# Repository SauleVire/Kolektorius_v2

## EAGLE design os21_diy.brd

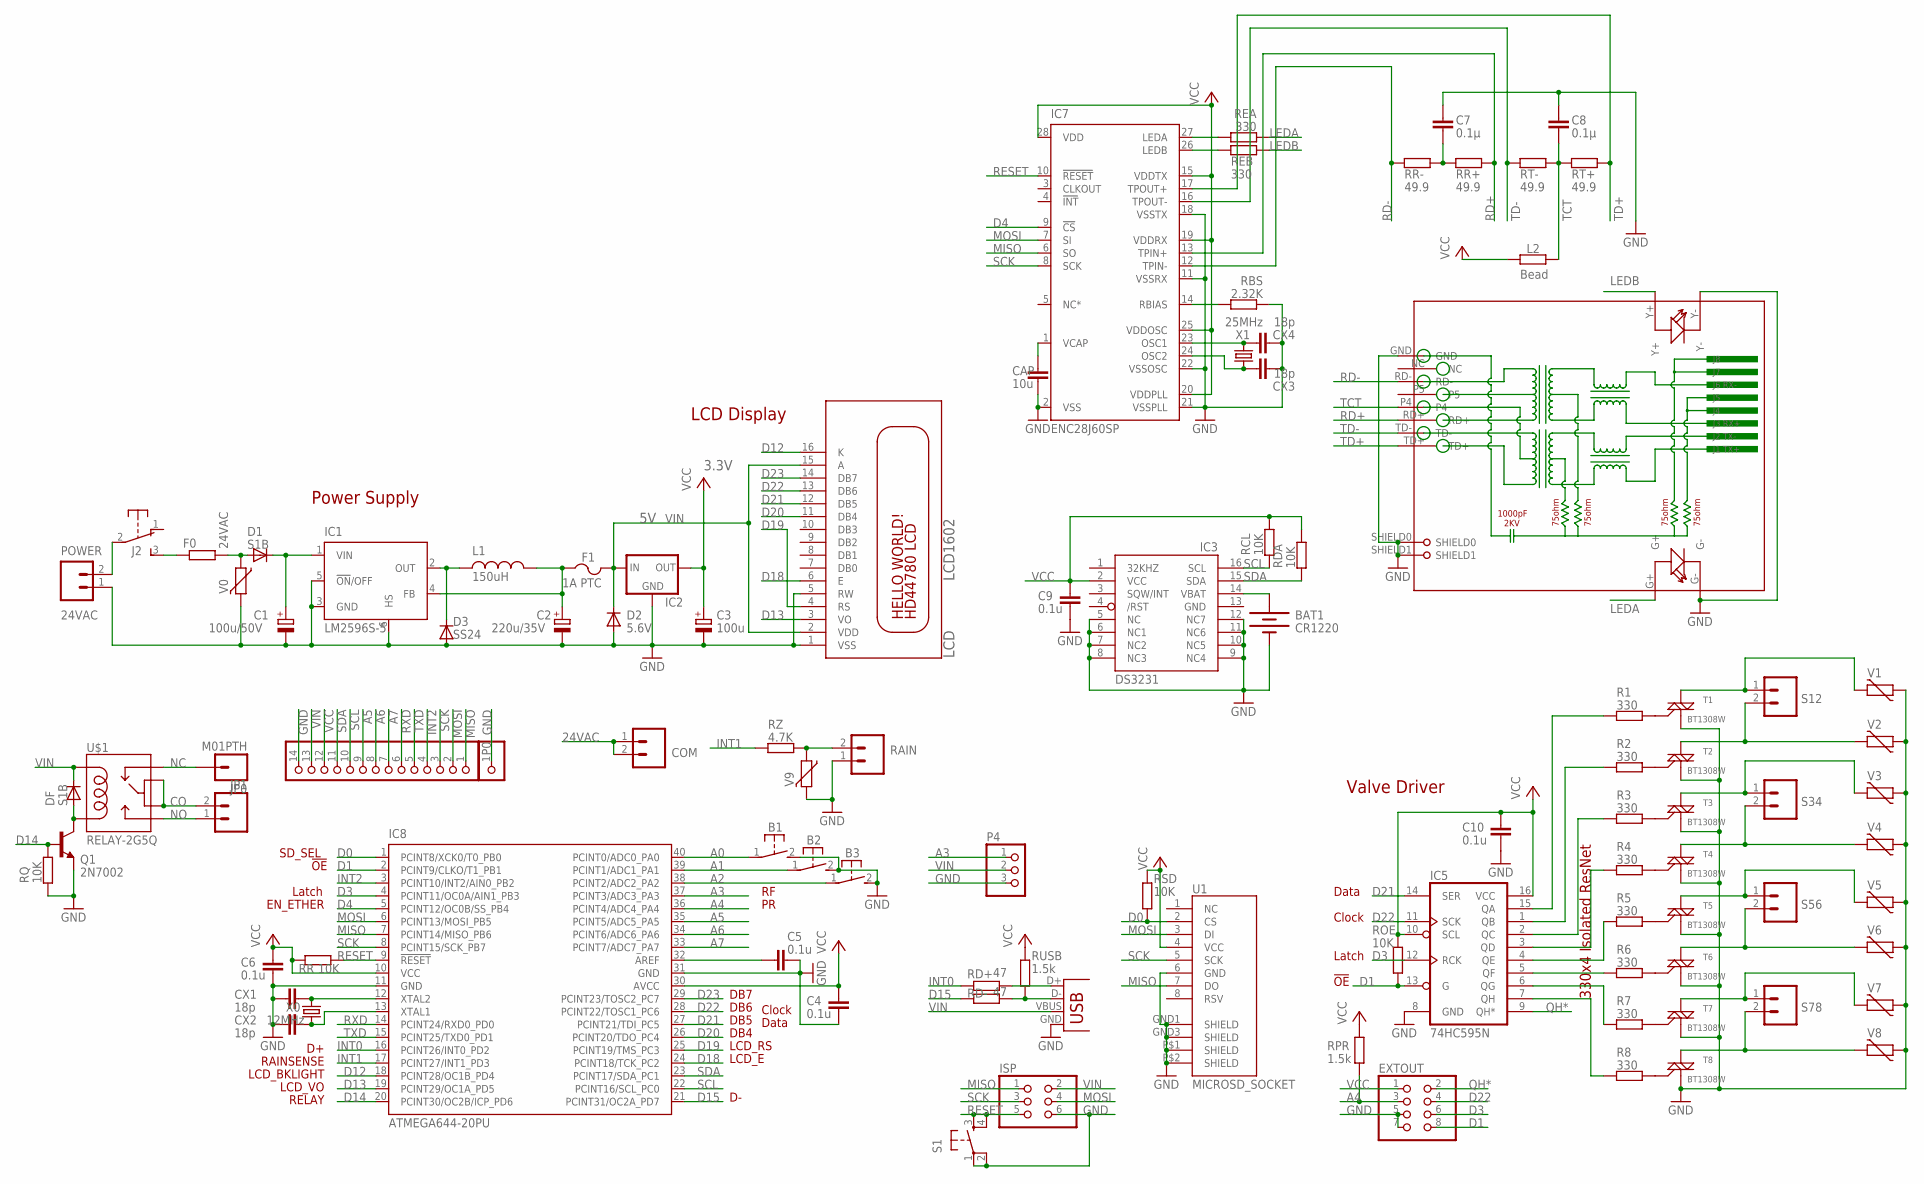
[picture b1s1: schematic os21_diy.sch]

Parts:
B1, B2, B3: 31-XX; B3F-31XX
BAT1: CR1220; BATTCON_12MM_SMT
C1: 100u/50V; E3,5-8
C2: 220u/35V; E3,5-8
C3: 100u; E2-5
C4, C5, C6, C9, C10: 0.1u; C0805
C7, C8: 0.1µ; C0805
CAP: 10u; C0805
COM: M025MM-X; SCREWTERMINAL-5MM-2-X
CX1, CX2, CX3, CX4: 18p; C0805
D1: S1B; DO-214AC
D2: 5.6V; MINIMELF
D3: SS24; DO-214AC
DF: S1B; DO-214AC
EXTOUT: PINHD-2X4; 2X04
F0: R-EU_0411/3V; 0411V
F1: 1A PTC; 1812
IC1: LM2596S-5; TO263-5
IC2: MCP1700SOT233; SOT23
IC3: DS3231/SO; SO16W
IC5: 74HC595N; SO16
IC7: ENC28J60SP; DIL28-3
IC8: ATMEGA644-20PU; DIL40
ISP: PINHD-2X3; 2X03
J2: EG1206
JP0: M01PTH; 1X01
JP1: M025MM-X; SCREWTERMINAL-5MM-2-X
L1: 150uH; CDRH125
L2: Bead; R0805
LCD: LCD1602; LCD1602A
P0: PINHD-1X14-CB; 1X14-CB
P1: PINHD-1X1CB; 1X01-CLEANBIG
P4: PINHD-1X3; 1X03
POWER: 24VAC; SCREWTERMINAL-4MM-2-X
Q1: 2N7002; SOT23-3
R1, R2, R3, R4, R5, R6, R7, R8: 330; R0805
RAIN: M025MM-X; SCREWTERMINAL-5MM-2-X
RBS: 2.32K; R0805
RCL: 10K; R0805
RD+: 47; R0805
RD-: 47; R0805
RDA: 10K; R0805
REA: 330; R0805
REB: 330; R0805
RJ45: HR911105A
ROE: 10K; R0805
RPR: 1.5k; R0805
RQ: 10K; R0805
RR: 10K; R0805
RR+: 49.9; R0805
RR-: 49.9; R0805
RSD: 10K; R0805
RT+: 49.9; R0805
RT-: 49.9; R0805
RUSB: 1.5k; R0805
RZ: 4.7K; R0805
S1: TAC_SWITCHSMD; TACTILE_SWITCH_SMD
S12, S34, S56, S78: M025MM-X; SCREWTERMINAL-5MM-2-X
T1, T2, T3, T4, T5, T6, T7, T8: BT1308W; TO-92
U1: MICROSD_SOCKET; MICRO-SD-SOCKET-TAOBAO
U$1: RELAY-2G5Q; RELAY-G5V
USB: USBPTH; USB-B-PTH
V0, V1, V2, V3, V4, V5, V6, V7, V8, V9: MOV; R-5
X0: 12MHz; HC49U-V
X1: 25MHz; HC49U-V

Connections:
24VAC: COM.1, COM.2, D1.A, F0.2, V0.1
A0: B1.1, IC8.40 (PCINT0/ADC0_PA0)
A1: B2.1, IC8.39 (PCINT1/ADC1_PA1)
A2: B3.1, IC8.38 (PCINT2/ADC2_PA2)
A3: IC8.37 (PCINT3/ADC3_PA3), P4.1
A4: EXTOUT.3, IC8.36 (PCINT4/ADC4_PA4), RPR.1
A5: IC8.35 (PCINT5/ADC5_PA5), P0.9
A6: IC8.34 (PCINT6/ADC6_PA6), P0.8
A7: IC8.33 (PCINT7/ADC7_PA7), P0.7
AREF: C5.1, IC8.32 (AREF)
CO: JP1.2, U$1.5, U$1.6
D0: IC8.1 (PCINT8/XCK0/T0_PB0), RSD.1, U1.2 (CS)
D1: EXTOUT.8, IC5.13 (G), IC8.2 (PCINT9/CLKO/T1_PB1), ROE.1
D3: EXTOUT.6, IC5.12 (RCK), IC8.4 (PCINT11/OC0A/AIN1_PB3)
D4: IC7.9 (!CS), IC8.5 (PCINT12/OC0B/SS_PB4)
D12: IC8.18 (PCINT28/OC1B_PD4), LCD.16 (K)
D13: IC8.19 (PCINT29/OC1A_PD5), LCD.3 (VO)
D14: IC8.20 (PCINT30/OC2B/ICP_PD6), Q1.1 (B), RQ.1
D15: IC8.21 (PCINT31/OC2A_PD7), RD-.1
D18: IC8.24 (PCINT18/TCK_PC2), LCD.6 (E)
D19: IC8.25 (PCINT19/TMS_PC3), LCD.4 (RS)
D20: IC8.26 (PCINT20/TDO_PC4), LCD.11 (DB4)
D21: IC5.14 (SER), IC8.27 (PCINT21/TDI_PC5), LCD.12 (DB5)
D22: EXTOUT.4, IC5.11 (SCK), IC8.28 (PCINT22/TOSC1_PC6), LCD.13 (DB6)
D23: IC8.29 (PCINT23/TOSC2_PC7), LCD.14 (DB7)
GND: B1.2 (S), B2.2 (S), B3.2 (S), BAT1.P$1 (-), C1.-, C2.-, C3.-, C4.2, C5.2, C6.2, C7.1, C8.1, C9.2, C10.2, CAP.2, CX1.2, CX2.2, CX3.2, CX4.2, D2.A, D3.A, EXTOUT.5, EXTOUT.7, IC1.3 (GND), IC1.5 (!ON!/OFF), IC1.6 (HS), IC2.1 (GND), IC3.5 (NC), IC3.6 (NC1), IC3.7 (NC2), IC3.8 (NC3), IC3.9 (NC4), IC3.10 (NC5), IC3.11 (NC6), IC3.12 (NC7), IC3.13 (GND), IC5.8 (GND), IC7.2 (VSS), IC7.11 (VSSRX), IC7.18 (VSSTX), IC7.21 (VSSPLL), IC7.22 (VSSOSC), IC8.11 (GND), IC8.31 (GND), ISP.6, LCD.1 (VSS), LCD.5 (RW), P0.14, P1.1, P4.3, POWER.1, Q1.2 (E), RAIN.1, RBS.2, RJ45.G-, RJ45.GND, RJ45.SHIELD0, RJ45.SHIELD1, RJ45.Y-, RQ.2, S1.1, S1.2, T1.1 (M1), T2.1 (M1), T3.1 (M1), T4.1 (M1), T5.1 (M1), T6.1 (M1), T7.1 (M1), T8.1 (M1), U1.6 (GND), U1.GND1 (SHIELD), U1.GND3 (SHIELD), U1.P$1 (SHIELD), U1.P$2 (SHIELD), USB.GND, V0.2, V1.1, V2.1, V3.1, V4.1, V5.1, V6.1, V7.1, V8.1, V9.2
INT0: IC8.16 (PCINT26/INT0_PD2), RD+.1
INT1: IC8.17 (PCINT27/INT1_PD3), RZ.2
INT2: IC8.3 (PCINT10/INT2/AIN0_PB2), P0.4
LEDA: REA.2, RJ45.G+
LEDB: REB.2, RJ45.Y+
MISO: IC7.6 (SO), IC8.7 (PCINT14/MISO_PB6), ISP.1, P0.1, U1.7 (DO)
MOSI: IC7.7 (SI), IC8.6 (PCINT13/MOSI_PB5), ISP.4, P0.2, U1.3 (DI)
unnamed: C1.+, D1.C, IC1.1 (VIN)
unnamed: C2.+, F1.1, IC1.4 (FB), L1.2
unnamed: R1.1, T1.2 (G)
unnamed: IC5.5 (QF), R6.2
unnamed: IC5.6 (QG), R7.2
unnamed: J2.2, POWER.2
unnamed: IC5.7 (QH), R8.2
unnamed: BAT1.P$2 (+), IC3.14 (VBAT)
unnamed: D3.C, IC1.2 (OUT), L1.1
unnamed: IC5.4 (QE), R5.2
unnamed: IC5.3 (QD), R4.2
unnamed: IC5.2 (QC), R3.2
unnamed: IC5.1 (QB), R2.2
unnamed: IC5.15 (QA), R1.2
unnamed: R2.1, T2.2 (G)
unnamed: S12.1, T1.3 (M2), V1.2
unnamed: S12.2, T2.3 (M2), V2.2
unnamed: S34.1, T3.3 (M2), V3.2
unnamed: IC7.14 (RBIAS), RBS.1
unnamed: S34.2, T4.3 (M2), V4.2
unnamed: R3.1, T3.2 (G)
unnamed: S56.1, T5.3 (M2), V5.2
unnamed: S56.2, T6.3 (M2), V6.2
unnamed: S78.1, T7.3 (M2), V7.2
unnamed: S78.2, T8.3 (M2), V8.2
unnamed: R4.1, T4.2 (G)
unnamed: R5.1, T5.2 (G)
unnamed: R6.1, T6.2 (G)
unnamed: R7.1, T7.2 (G)
unnamed: RAIN.2, RZ.1, V9.1
unnamed: F0.1, J2.3 (S)
unnamed: CAP.1, IC7.1 (VCAP)
unnamed: IC7.27 (LEDA), REA.1
unnamed: DF.A, Q1.3 (C), U$1.9
unnamed: IC7.26 (LEDB), REB.1
unnamed: RD+.2, USB.D+
unnamed: CX3.1, IC7.24 (OSC2), X1.2
unnamed: CX4.1, IC7.23 (OSC1), X1.1
unnamed: R8.1, T8.2 (G)
unnamed: RD-.2, RUSB.1, USB.D-
unnamed: CX1.1, IC8.12 (XTAL2), X0.2
unnamed: CX2.1, IC8.13 (XTAL1), X0.1
unnamed: C7.2, RR+.1, RR-.2
NC: JP0.1, U$1.1
NO: JP1.1, U$1.10
QH*: EXTOUT.2, IC5.9 (QH*)
RD+: IC7.13 (TPIN+), RJ45.RD+, RR+.2
RD-: IC7.12 (TPIN-), RJ45.RD-, RR-.1
RESET: IC7.10 (!RESET), IC8.9 (!RESET), ISP.5, RR.2, S1.3, S1.4
RXD: IC8.14 (PCINT24/RXD0_PD0), P0.6
SCK: IC7.8 (SCK), IC8.8 (PCINT15/SCK_PB7), ISP.3, P0.3, U1.5 (SCK)
SCL: IC3.16 (SCL), IC8.22 (PCINT16/SCL_PC0), P0.10, RCL.2
SDA: IC3.15 (SDA), IC8.23 (PCINT17/SDA_PC1), P0.11, RDA.2
TCT: C8.2, L2.1, RJ45.P4, RT+.1, RT-.2
TD+: IC7.17 (TPOUT+), RJ45.TD+, RT+.2
TD-: IC7.16 (TPOUT-), RJ45.TD-, RT-.1
TXD: IC8.15 (PCINT25/TXD0_PD1), P0.5
VCC: C3.+, C4.1, C6.1, C9.1, C10.1, EXTOUT.1, IC2.2 (OUT), IC3.2 (VCC), IC5.10 (SCL), IC5.16 (VCC), IC7.15 (VDDTX), IC7.19 (VDDRX), IC7.20 (VDDPLL), IC7.25 (VDDOSC), IC7.28 (VDD), IC8.10 (VCC), IC8.30 (AVCC), L2.2, P0.12, RCL.1, RDA.1, ROE.2, RPR.2, RR.1, RSD.2, RUSB.2, U1.4 (VCC)
VIN: D2.C, DF.C, F1.2, IC2.3 (IN), ISP.2, LCD.2 (VDD), LCD.15 (A), P0.13, P4.2, U$1.2, USB.VBUS

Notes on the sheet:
Power Supply
Valve Driver
Data
Clock
Latch
DB4
330x4 Isolated ResNet
LCD Display
EN_ETHER
3.3V
DB7
LCD_E
LCD_RS
DB6
DB5
!OE
RAINSENSE
LCD_BKLIGHT
LCD_VO
SD_SEL
RELAY

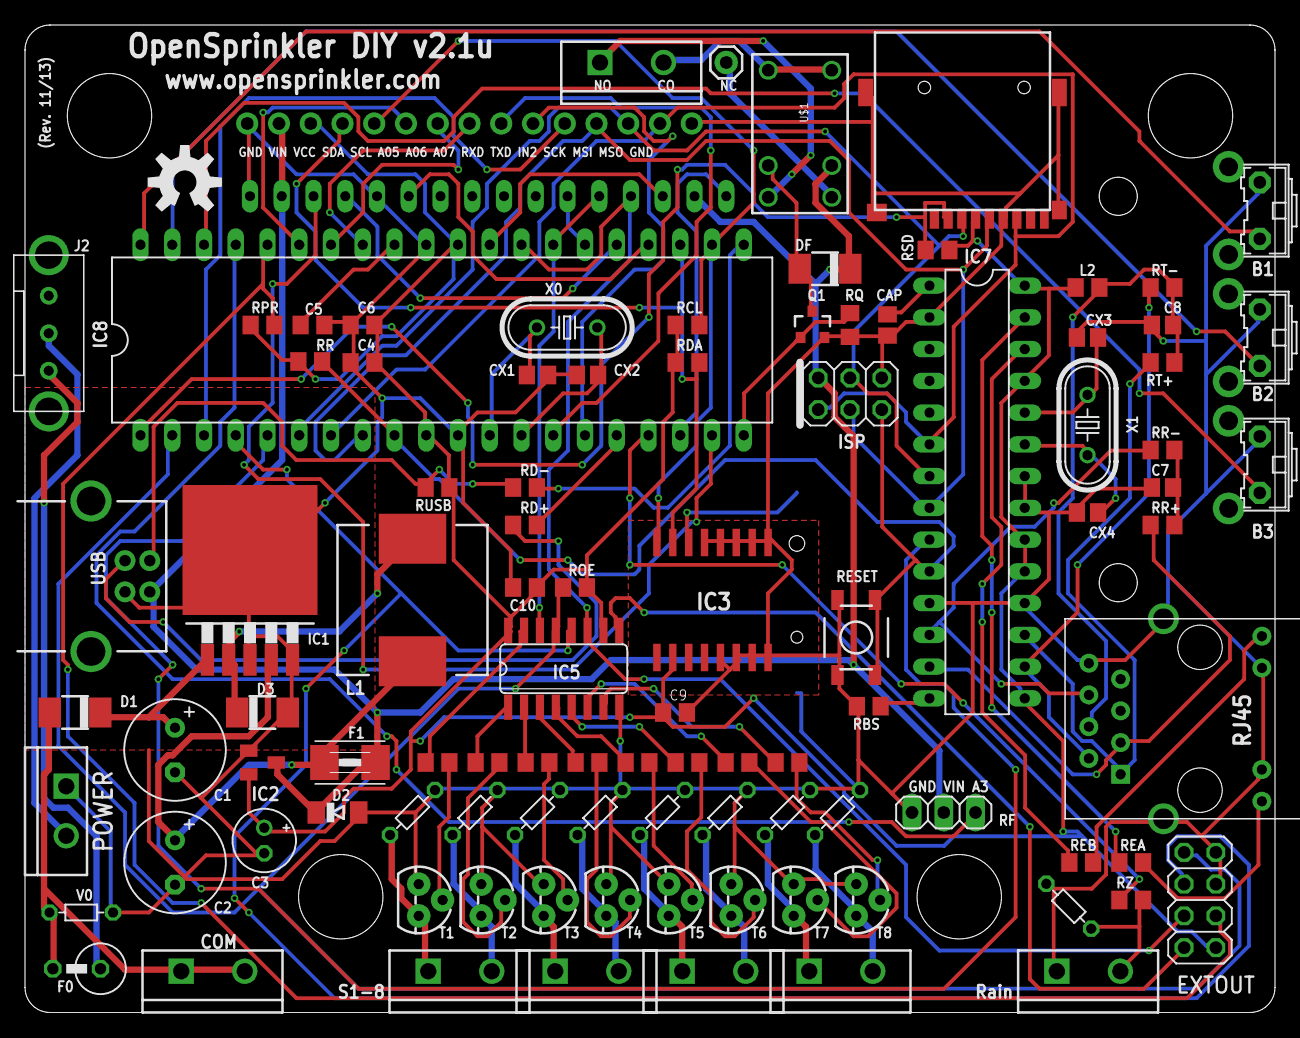
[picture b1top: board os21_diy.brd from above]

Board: 2 copper layers, 100.0 x 79.0 mm, 101 parts (1 on the bottom side), 92 nets.

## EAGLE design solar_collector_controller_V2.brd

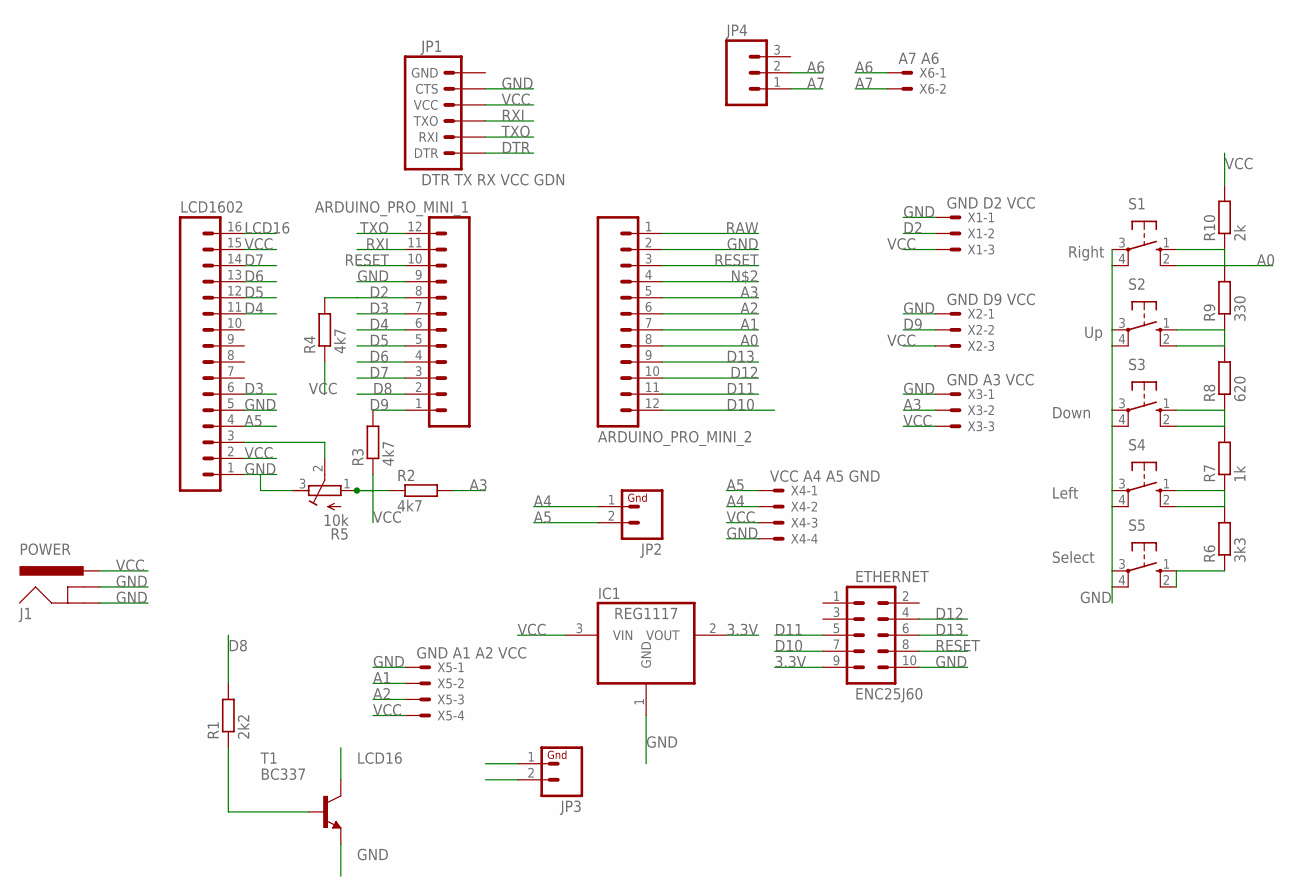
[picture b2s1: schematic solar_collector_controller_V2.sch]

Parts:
ARDUINO_PRO_MINI_1, ARDUINO_PRO_MINI_2: M12PTH; 1X12
ETHERNET: ENC25J60; AVR_ICSP
IC1: REG1117; SOT223
J1: POWER; POWER_JACK_PTH_LOCK
JP1: DTR TX RX VCC GDN; 1X06
JP2, JP3: M02PTH; 1X02
JP4: M03PTH; 1X03
LCD1602: HEADER-16P-2.54; 16P-2.54
R1: 2k2; 0207/10
R2, R3, R4: 4k7; 0207/10
R5: 10k; RTRIM64W
R6: 3k3; 0207/10
R7: 1k; 0207/10
R8: 620; 0207/10
R9: 330; 0207/10
R10: 2k; 0207/10
S1: Right; B3F-10XX
S2: Up; B3F-10XX
S3: Down; B3F-10XX
S4: Left; B3F-10XX
S5: Select; B3F-10XX
T1: BC337; TO92
X1: GND D2 VCC; 22-23-2031
X2: GND D9 VCC; 22-23-2031
X3: GND A3 VCC; 22-23-2031
X4: VCC A4 A5 GND; 22-23-2041
X5: GND A1 A2 VCC; 22-23-2041
X6: A7 A6; 22-23-2021

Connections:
3.3V: ETHERNET.9, IC1.2 (VOUT), JP3.1
A0: ARDUINO_PRO_MINI_2.8, R9.2, R10.1, S1.1 (S), S1.2 (S1)
A1: ARDUINO_PRO_MINI_2.7, X5.2
A2: ARDUINO_PRO_MINI_2.6, X5.3
A3: ARDUINO_PRO_MINI_2.5, R2.2, X3.2
A4: JP2.1, X4.2
A5: JP2.2, LCD1602.4, X4.1
A6: JP4.2, X6.1
A7: JP4.1, X6.2
D2: ARDUINO_PRO_MINI_1.8, R4.2, X1.2
D3: ARDUINO_PRO_MINI_1.7, LCD1602.6
D4: ARDUINO_PRO_MINI_1.6, LCD1602.11
D5: ARDUINO_PRO_MINI_1.5, LCD1602.12
D6: ARDUINO_PRO_MINI_1.4, LCD1602.13
D7: ARDUINO_PRO_MINI_1.3, LCD1602.14
D8: ARDUINO_PRO_MINI_1.2, R1.2
D9: ARDUINO_PRO_MINI_1.1, R3.2, X2.2
D10: ARDUINO_PRO_MINI_2.12, ETHERNET.7
D11: ARDUINO_PRO_MINI_2.11, ETHERNET.5
D12: ARDUINO_PRO_MINI_2.10, ETHERNET.4
D13: ARDUINO_PRO_MINI_2.9, ETHERNET.6
DTR: JP1.1 (DTR)
GND: ARDUINO_PRO_MINI_1.9, ARDUINO_PRO_MINI_2.2, ETHERNET.10, IC1.1 (GND), J1.GND, J1.GNDBREAK, JP1.5 (CTS), JP3.2, LCD1602.1, LCD1602.5, R5.3 (A), S1.3, S1.4 (P1), S2.3, S2.4 (P1), S3.3, S3.4 (P1), S4.3, S4.4 (P1), S5.3, S5.4 (P1), T1.1 (E), X1.1, X2.1, X3.1, X4.4, X5.1
LCD16: LCD1602.16, T1.3 (C)
unnamed: LCD1602.3, R5.2 (S)
unnamed: R1.1, T1.2 (B)
unnamed: R6.1, S5.1 (S), S5.2 (S1)
unnamed: R6.2, R7.1, S4.1 (S), S4.2 (S1)
unnamed: R7.2, R8.1, S3.1 (S), S3.2 (S1)
unnamed: R8.2, R9.1, S2.1 (S), S2.2 (S1)
RAW: ARDUINO_PRO_MINI_2.1
RESET: ARDUINO_PRO_MINI_1.10, ARDUINO_PRO_MINI_2.3, ETHERNET.8
RXI: ARDUINO_PRO_MINI_1.11, JP1.3 (TXO)
TXO: ARDUINO_PRO_MINI_1.12, JP1.2 (RXI)
VCC: IC1.3 (VIN), J1.PWR, JP1.4 (VCC), LCD1602.2, LCD1602.15, R2.1, R3.1, R4.1, R5.1 (E), R10.2, X1.3, X2.3, X3.3, X4.3, X5.4

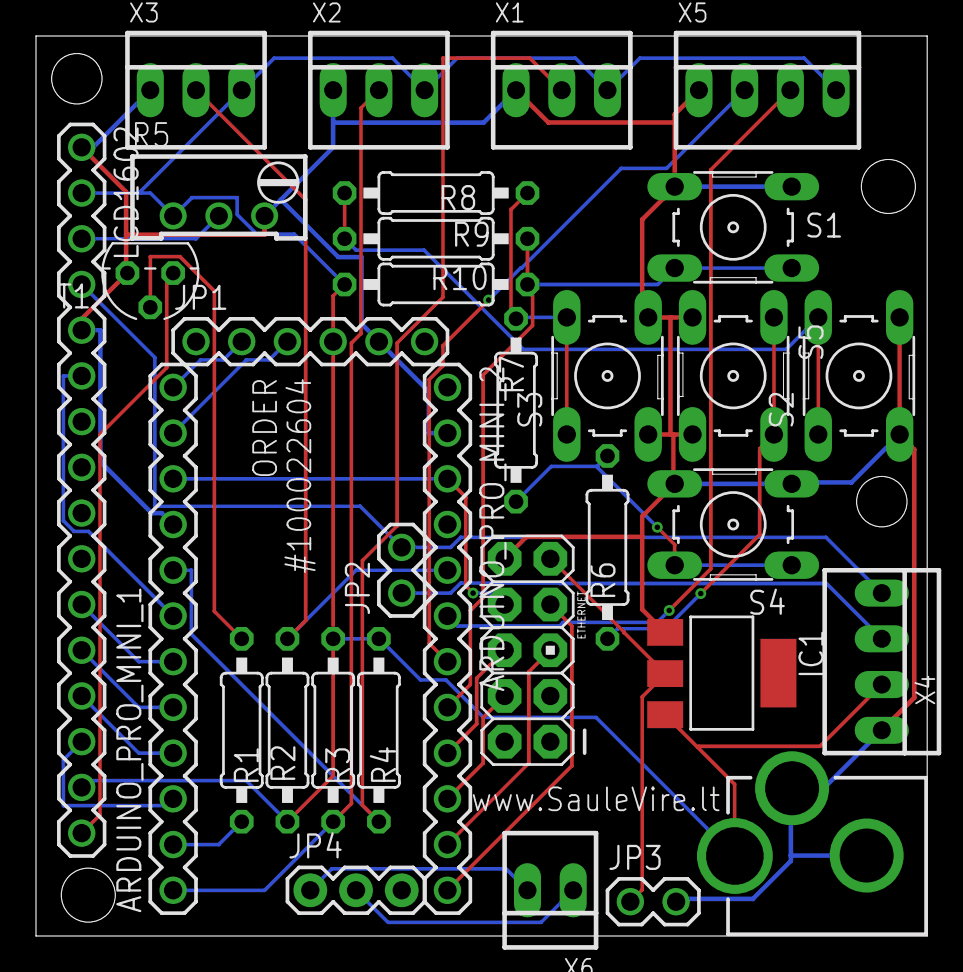
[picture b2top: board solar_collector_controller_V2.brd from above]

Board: 2 copper layers, 49.5 x 50.0 mm, 32 parts (0 on the bottom side), 33 nets.

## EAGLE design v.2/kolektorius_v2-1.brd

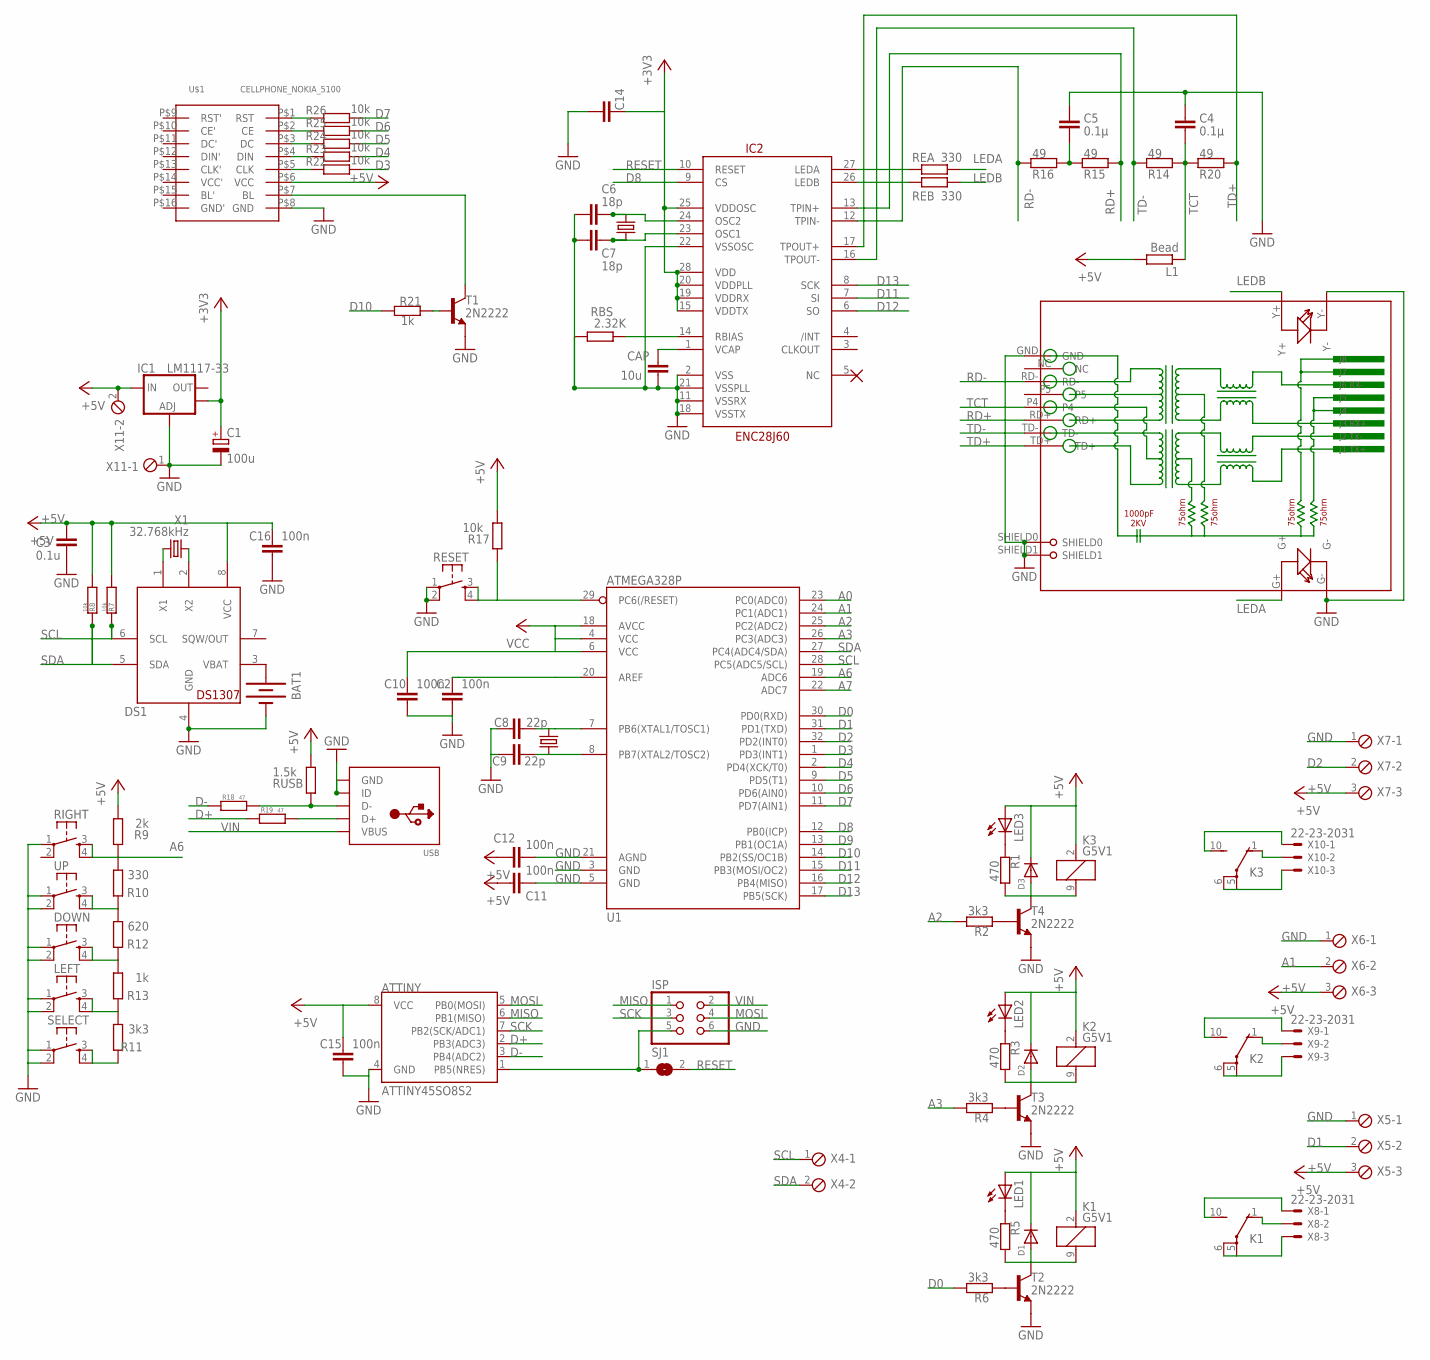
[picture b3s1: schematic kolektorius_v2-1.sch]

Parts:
ATTINY: ATTINY45SO8S2; SO8S2
BAT1: BATTERYBATTERY_12MM_SMT; BATTCON_12MM_SMT
C1: 100u; E2-5
C2, C10, C11, C12, C14, C15, C16: 100n; C0805
C3: 0.1u; C0805
C4, C5: 0.1µ; C0805
C6, C7: 18p; C0805
C8, C9: 22p; C0805
CAP: 10u; C0805
D1, D2, D3: DIODEDO-1N4148; DO-1N4148
DOWN: TAC_SWITCHPTH; TACTILE-PTH
DS1: DS1307; SO08
IC1: LM1117-33; SOT223
IC2: ENC28J60; SSOP28DB
ISP: PINHD-2X3; 2X03
K1, K2, K3: G5V1
L1: Bead; R0805
LED1, LED2, LED3: LEDSMT1206; 1206
LEFT: TAC_SWITCHPTH; TACTILE-PTH
R1, R3, R5: 470; R0805
R2, R4, R6, R11: 3k3; R0805
R7, R8, R17, R22, R23, R24, R25, R26: 10k; R0805
R9: 2k; R0805
R10: 330; R0805
R12: 620; R0805
R13, R21: 1k; R0805
R14, R15, R16, R20: 49; R0805
R18, R19: 47; R0805
RBS: 2.32K; R0805
REA: 330; R0805
REB: 330; R0805
RESET: TAC_SWITCHPTH; TACTILE-PTH
RIGHT: TAC_SWITCHPTH; TACTILE-PTH
RJ1: HR911105A
RUSB: 1.5k; R0805
SELECT: TAC_SWITCHPTH; TACTILE-PTH
SJ1: SJ
T1, T2, T3, T4: 2N2222; TO92-EBC-OVAL
U1: ATMEGA328P; TQFP32-08
U$1: CELLPHONE_NOKIA_5100; CELLPHONE_NOKIA_5100_SPARKFUN
UP: TAC_SWITCHPTH; TACTILE-PTH
USB: USBMOLEX; USB-MINIB-THM-MOLEX
X1: 32.768kHz; TC26H
X2: 16MHz; HC49US
X3: 25MHz; HC49US
X4, X11: MPT2; 2POL254
X5, X6, X7: MPT3; 3POL254
X8, X9, X10: 22-23-2031

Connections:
+3V3: C1.+, C14.1, IC1.4 (OUT), IC2.15 (VDDTX), IC2.19 (VDDRX), IC2.20 (VDDPLL), IC2.25 (VDDOSC), IC2.28 (VDD)
+5V: ATTINY.8 (VCC), C3.1, C11.2, C12.2, C15.1, C16.1, D1.C, D2.C, D3.C, DS1.8 (VCC), IC1.3 (IN), K1.2 (1), K2.2 (1), K3.2 (1), L1.2, LED1.A, LED2.A, R7.2, R8.2, U$1.P$6 (VCC), X5.3, X6.3, X7.3, X11.2
A0: U1.23 (PC0(ADC0))
A1: U1.24 (PC1(ADC1)), X6.2
A2: R2.2, U1.25 (PC2(ADC2))
A3: R4.2, U1.26 (PC3(ADC3))
A6: R9.1, R10.2, RIGHT.3, RIGHT.4, U1.19 (ADC6)
A7: U1.22 (ADC7)
D0: R6.2, U1.30 (PD0(RXD))
D1: U1.31 (PD1(TXD)), X5.2
D2: U1.32 (PD2(INT0)), X7.2
D3: R22.2, U1.1 (PD3(INT1))
D4: R23.2, U1.2 (PD4(XCK/T0))
D5: R24.2, U1.9 (PD5(T1))
D6: R25.2, U1.10 (PD6(AIN0))
D7: R26.2, U1.11 (PD7(AIN1))
D8: IC2.9 (CS), U1.12 (PB0(ICP))
D9: U1.13 (PB1(OC1A))
D10: R21.2, U1.14 (PB2(SS/OC1B))
D11: IC2.7 (SI), U1.15 (PB3(MOSI/OC2))
D12: IC2.6 (SO), U1.16 (PB4(MISO))
D13: IC2.8 (SCK), U1.17 (PB5(SCK))
D+: ATTINY.2 (PB3(ADC3)), R19.1
D-: ATTINY.3 (PB4(ADC2)), R18.1
GND: ATTINY.4 (GND), BAT1.P$1 (-), C1.-, C2.2, C3.2, C4.1, C5.1, C6.2, C7.2, C8.1, C9.1, C10.2, C11.1, C12.1, C14.2, C15.2, C16.2, CAP.2, DOWN.1, DOWN.2, DS1.4 (GND), IC1.1 (ADJ), IC2.2 (VSS), IC2.11 (VSSRX), IC2.18 (VSSTX), IC2.21 (VSSPLL), IC2.22 (VSSOSC), ISP.6, LEFT.1, LEFT.2, RBS.1, RESET.1, RESET.2, RIGHT.1, RJ1.G-, RJ1.GND, RJ1.SHIELD0, RJ1.SHIELD1, RJ1.Y-, SELECT.1, SELECT.2, T1.E, T2.E, T3.E, T4.E, U1.3 (GND), U1.5 (GND), U1.21 (AGND), U$1.P$8 (GND), UP.1, UP.2, USB.GND, USB.ID, X5.1, X6.1, X7.1, X11.1
LEDA: REA.2, RJ1.G+
LEDB: REB.2, RJ1.Y+
MISO: ATTINY.6 (PB1(MISO)), ISP.1
MOSI: ATTINY.5 (PB0(MOSI)), ISP.4
unnamed: LEFT.3, LEFT.4, R11.2, R13.1
unnamed: D2.A, K2.9 (2), R3.2, T3.C
unnamed: R4.1, T3.B
unnamed: K2.5, K2.6, X9.3
unnamed: K2.1 (O), X9.2
unnamed: DOWN.3, DOWN.4, R12.1, R13.2
unnamed: LED2.C, R3.1
unnamed: DS1.1 (X1), X1.2
unnamed: R10.1, R12.2, UP.3, UP.4
unnamed: D1.A, K1.9 (2), R5.2, T2.C
unnamed: D3.A, K3.9 (2), R1.2, T4.C
unnamed: R2.1, T4.B
unnamed: K2.10 (S), X9.1
unnamed: K1.10 (S), X8.1
unnamed: K3.10 (S), X10.1
unnamed: R6.1, T2.B
unnamed: R11.1, SELECT.3, SELECT.4
unnamed: K3.5, K3.6, X10.3
unnamed: K3.1 (O), X10.2
unnamed: LED3.C, R1.1
unnamed: R22.1, U$1.P$5 (CLK)
unnamed: R25.1, U$1.P$2 (CE)
unnamed: R24.1, U$1.P$3 (DC)
unnamed: R23.1, U$1.P$4 (DIN)
unnamed: T1.C, U$1.P$7 (BL)
unnamed: K1.5, K1.6, X8.3
unnamed: K1.1 (O), X8.2
unnamed: DS1.2 (X2), X1.1
unnamed: LED1.C, R5.1
unnamed: C9.2, U1.8 (PB7(XTAL2/TOSC2)), X2.1
unnamed: C8.2, U1.7 (PB6(XTAL1/TOSC1)), X2.2
unnamed: IC2.27 (LEDA), REA.1
unnamed: C2.1, U1.20 (AREF)
unnamed: BAT1.P$2 (+), DS1.3 (VBAT)
unnamed: IC2.26 (LEDB), REB.1
unnamed: R19.2, USB.D+
unnamed: CAP.1, IC2.1 (VCAP)
unnamed: C6.1, IC2.24 (OSC2), X3.2
unnamed: C7.1, IC2.23 (OSC1), X3.1
unnamed: R21.1, T1.B
unnamed: R18.2, RUSB.1, USB.D-
unnamed: R17.1, RESET.3, RESET.4, U1.29 (PC6(/RESET))
unnamed: ATTINY.1 (PB5(NRES)), ISP.5, SJ1.1
unnamed: C5.2, R15.1, R16.2
unnamed: IC2.14 (RBIAS), RBS.2
RD+: IC2.13 (TPIN+), R15.2, RJ1.RD+
RD-: IC2.12 (TPIN-), R16.1, RJ1.RD-
RESET: IC2.10 (RESET), SJ1.2
SCK: ATTINY.7 (PB2(SCK/ADC1)), ISP.3
SCL: DS1.6 (SCL), R7.1, U1.28 (PC5(ADC5/SCL))
SDA: DS1.5 (SDA), R8.1, U1.27 (PC4(ADC4/SDA))
TCT: C4.2, L1.1, R14.2, R20.1, RJ1.P4
TD+: IC2.17 (TPOUT+), R20.2, RJ1.TD+
TD-: IC2.16 (TPOUT-), R14.1, RJ1.TD-
V$: R26.1, U$1.P$1 (RST)
VCC: C10.1, R9.2, R17.2, RUSB.2, U1.4 (VCC), U1.6 (VCC), U1.18 (AVCC)
VIN: ISP.2, USB.VBUS

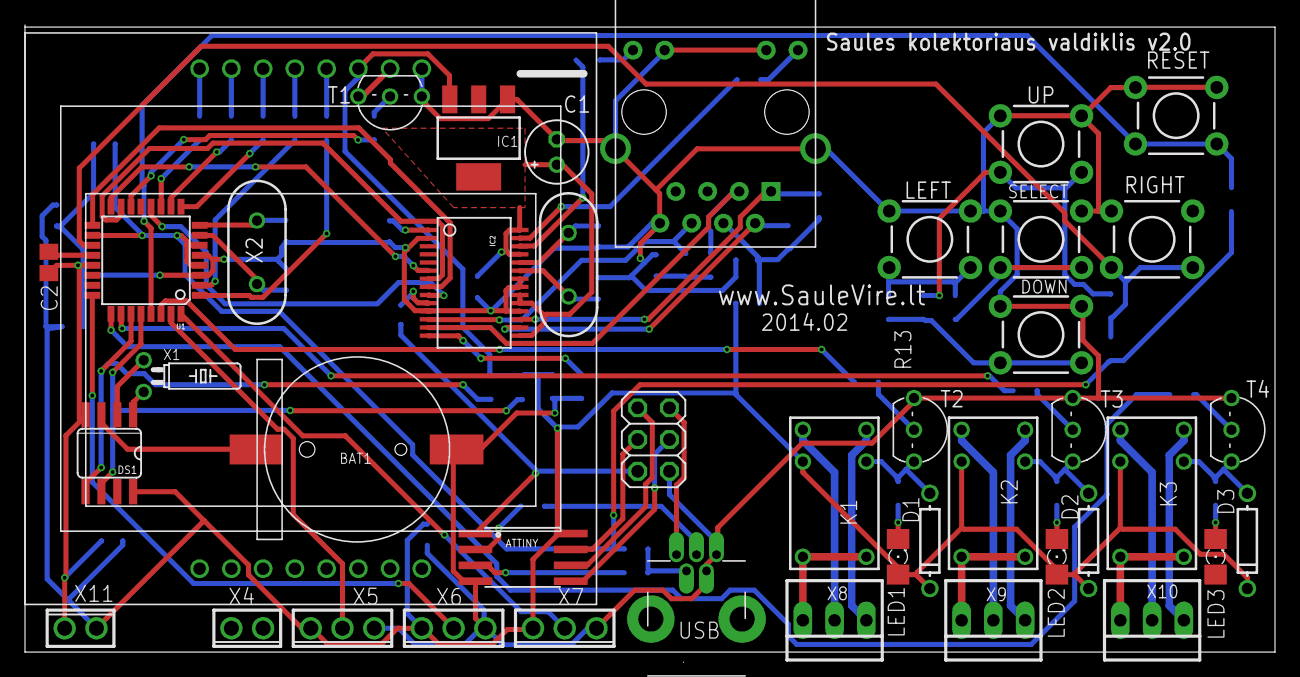
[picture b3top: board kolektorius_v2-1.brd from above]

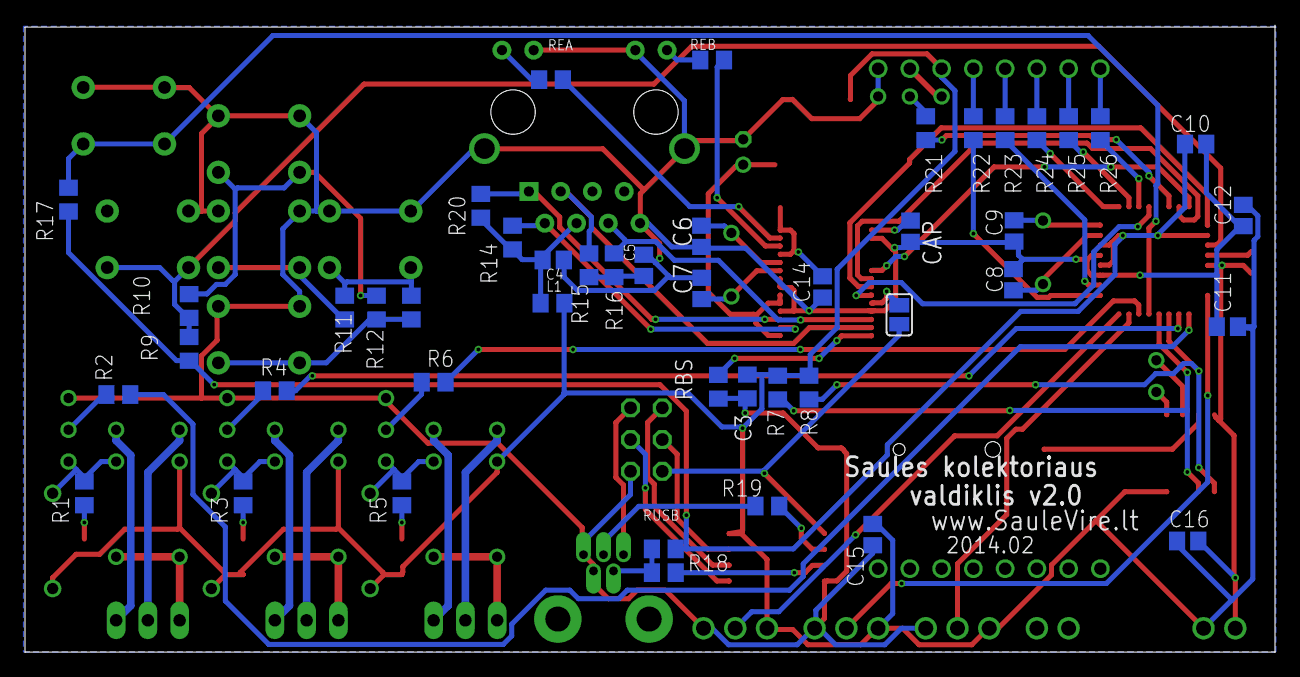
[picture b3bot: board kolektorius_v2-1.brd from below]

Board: 2 copper layers, 100.0 x 50.2 mm, 88 parts (46 on the bottom side), 83 nets.

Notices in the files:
parts and their libraries:
SparkFun-Connectors: Licensing: CC v3.0 Share-Alike You are welcome to use this library for commercial purposes.
